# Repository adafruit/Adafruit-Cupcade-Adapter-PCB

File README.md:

## Adafruit Cupcade Arcade Adapter V1 PCB
<a href="http://www.adafruit.com/products/1916"><br/>
Click here to purchase one from the Adafruit shop</a>

This is the PCB and small parts pack from original V1 Cupcade. These parts were used with the original "Raspberry Pi 1" design, not the version for Pi A+, 2, 3, or Zero!

Great for anyone who needs a replacement PCB or wants to mod or build out their Cupcade. 

PCB files for the Adafruit Cupcade Adapter. The format is EagleCAD schematic and board layout
- http://www.adafruit.com/product/1916

### License

Adafruit invests time and resources providing this open source design, please support Adafruit and open-source hardware by purchasing products from [Adafruit](https://www.adafruit.com)!

All text above must be included in any redistribution

Designed by Limor Fried/Ladyada for Adafruit Industries.
Creative Commons Attribution/Share-Alike, all text above must be included in any redistribution. 
See license.txt for additional information.

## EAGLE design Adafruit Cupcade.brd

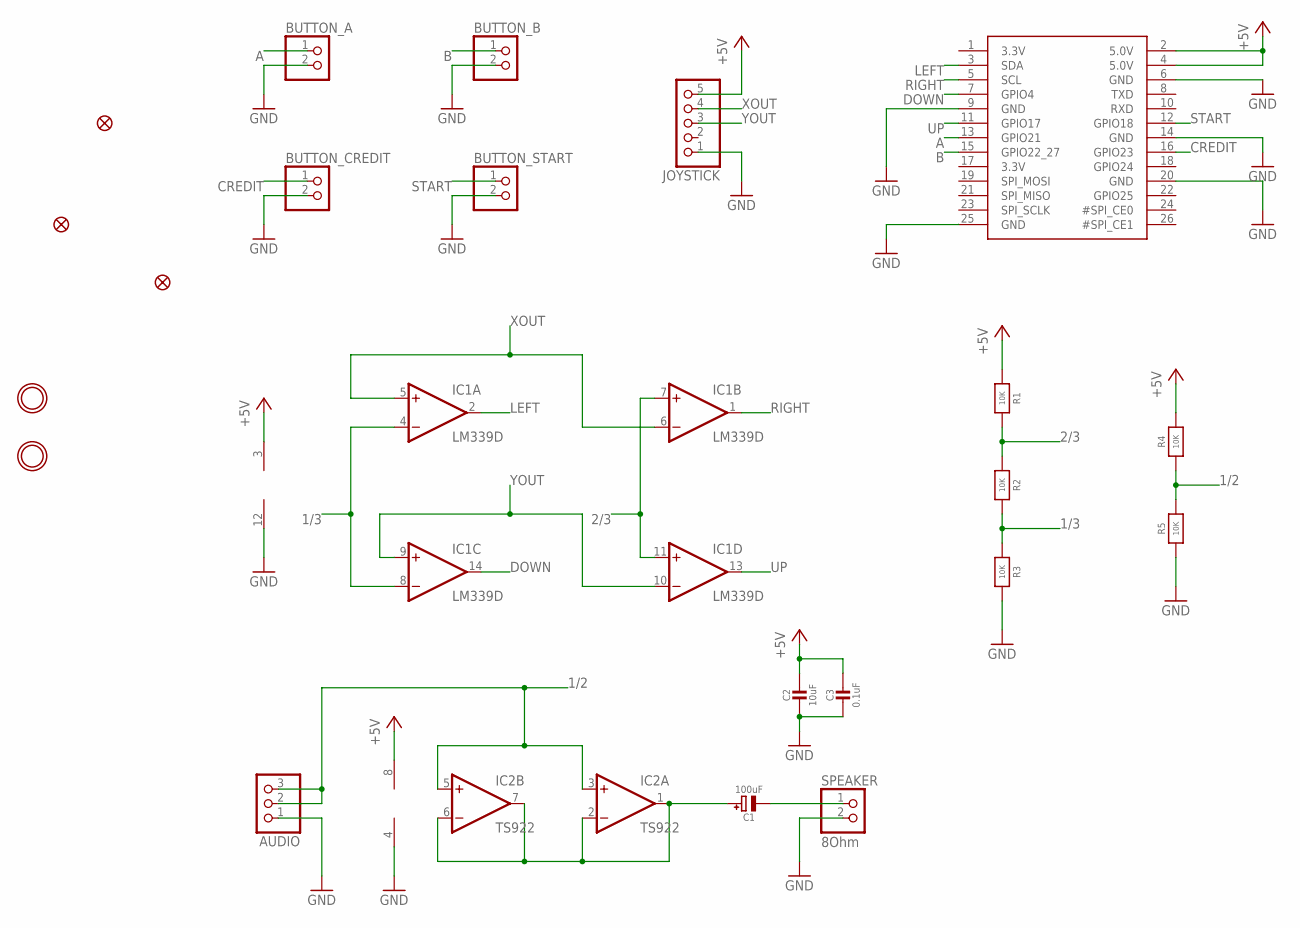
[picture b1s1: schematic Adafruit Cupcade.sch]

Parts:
AUDIO: HEADER-1X3; 1X03_OVAL
BUTTON_A: HEADER-1X2; 1X02_OVAL
BUTTON_B: HEADER-1X2; 1X02_OVAL
BUTTON_CREDIT: HEADER-1X2; 1X02_OVAL
BUTTON_START: HEADER-1X2; 1X02_OVAL
C1: 100uF; PANASONIC_C
C2: 10uF; 0805-NO
C3: 0.1uF; 0805-NO
FID1, FID2, FID3: FIDUCIAL""; FIDUCIAL_1MM
IC1: LM339D; SO14
IC2: TS922; SO08
JOYSTICK: HEADER-1X5; 1X05_OVAL
JP1: RASBERRYPI_IDC
R1, R2, R3, R4, R5: 10K; 0805-NO
SPEAKER: 8Ohm; 1X02_OVAL
U$2, U$3: MOUNTINGHOLE2.5; MOUNTINGHOLE_2.5_PLATED

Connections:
1/2: AUDIO.2, AUDIO.3, IC2.3 (+IN), IC2.5 (+IN), R4.1, R5.2
1/3: IC1.4 (-IN), IC1.8 (-IN), R2.2, R3.1
2/3: IC1.7 (+IN), IC1.11 (+IN), R1.2, R2.1
+5V: C2.1, C3.1, IC1.3 (V+), IC2.8 (V+), JOYSTICK.5, JP1.2 (5.0V), JP1.4 (5.0V), R1.1, R4.2
A: BUTTON_A.1, JP1.13 (GPIO21)
B: BUTTON_B.1, JP1.15 (GPIO22_27)
CREDIT: BUTTON_CREDIT.1, JP1.16 (GPIO23)
DOWN: IC1.14 (OUT), JP1.7 (GPIO4)
GND: AUDIO.1, BUTTON_A.2, BUTTON_B.2, BUTTON_CREDIT.2, BUTTON_START.2, C2.2, C3.2, IC1.12 (GND), IC2.4 (V-), JOYSTICK.1, JP1.6 (GND), JP1.9 (GND), JP1.14 (GND), JP1.20 (GND), JP1.25 (GND), R3.2, R5.1, SPEAKER.2
LEFT: IC1.2 (OUT), JP1.3 (SDA)
unnamed: C1.-, SPEAKER.1
unnamed: C1.+, IC2.1 (OUT), IC2.2 (-IN), IC2.6 (-IN), IC2.7 (OUT)
RIGHT: IC1.1 (OUT), JP1.5 (SCL)
START: BUTTON_START.1, JP1.12 (GPIO18)
UP: IC1.13 (OUT), JP1.11 (GPIO17)
XOUT: IC1.5 (+IN), IC1.6 (-IN), JOYSTICK.4
YOUT: IC1.9 (+IN), IC1.10 (-IN), JOYSTICK.3

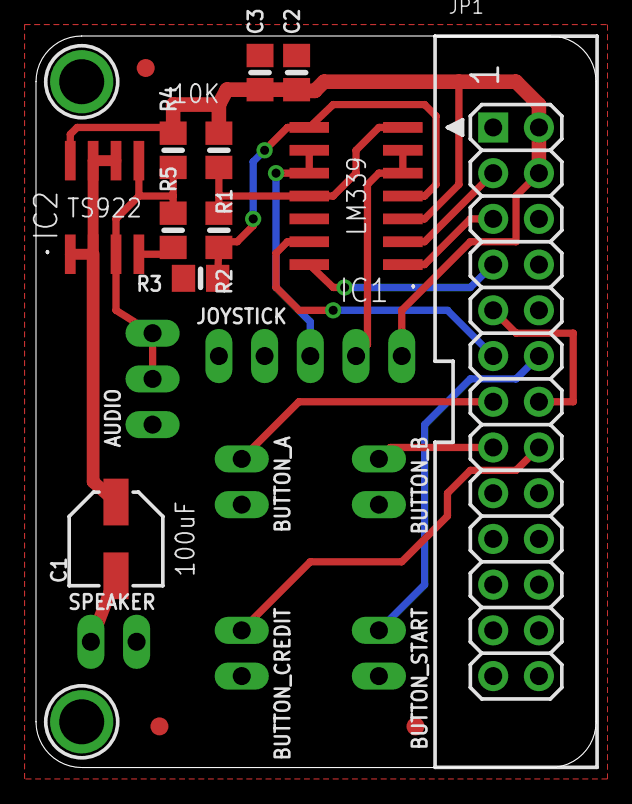
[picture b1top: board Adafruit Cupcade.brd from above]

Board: 2 copper layers, 31.1 x 40.6 mm, 24 parts (1 on the bottom side), 17 nets.

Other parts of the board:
U$1: DRAGON_300MIL

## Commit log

2016-08-19 cupcade!

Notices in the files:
parts and their libraries:
microbuilder: This work is placed in the public domain, and may be freely used for commercial and non-commercial work with the following conditions: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
